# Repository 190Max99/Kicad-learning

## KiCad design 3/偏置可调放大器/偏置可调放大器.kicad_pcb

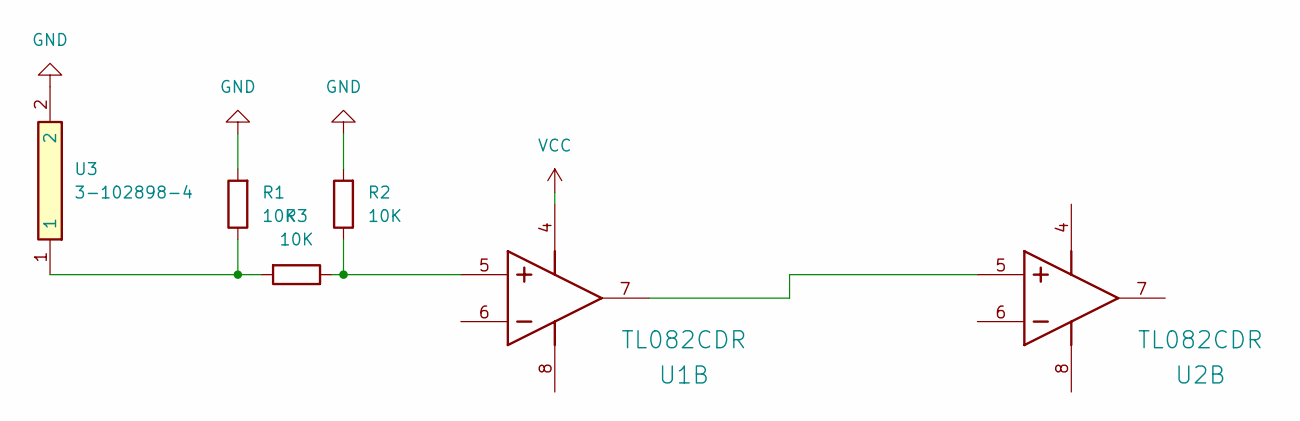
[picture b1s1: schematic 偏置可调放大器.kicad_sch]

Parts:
R1, R2, R3: 10K; R_01005_0402Metric
U1, U2: TL082CDR; voltage_gain 106.02 dB; MPN TL082CDR
U3: 3-102898-4; MPN 3-102898-4

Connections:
GND: R1.2, R2.2, U3.2
unnamed: R1.1, R3.2, U3.1
unnamed: R2.1, R3.1, U1.5 (IN2+)
unnamed 3: U1.7 (OUT2), U2.5 (IN2+); also elsewhere on the board
VCC: U1.4 (VCC-)

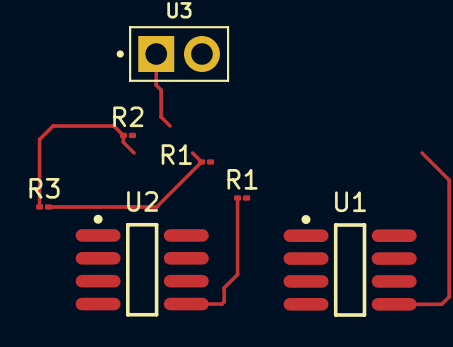
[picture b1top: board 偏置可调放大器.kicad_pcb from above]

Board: 2 copper layers, 7 parts (0 on the bottom side), 4 nets.

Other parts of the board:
R1#2: 100; R_01005_0402Metric

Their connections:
unnamed 3: R1#2.1; also elsewhere on the board

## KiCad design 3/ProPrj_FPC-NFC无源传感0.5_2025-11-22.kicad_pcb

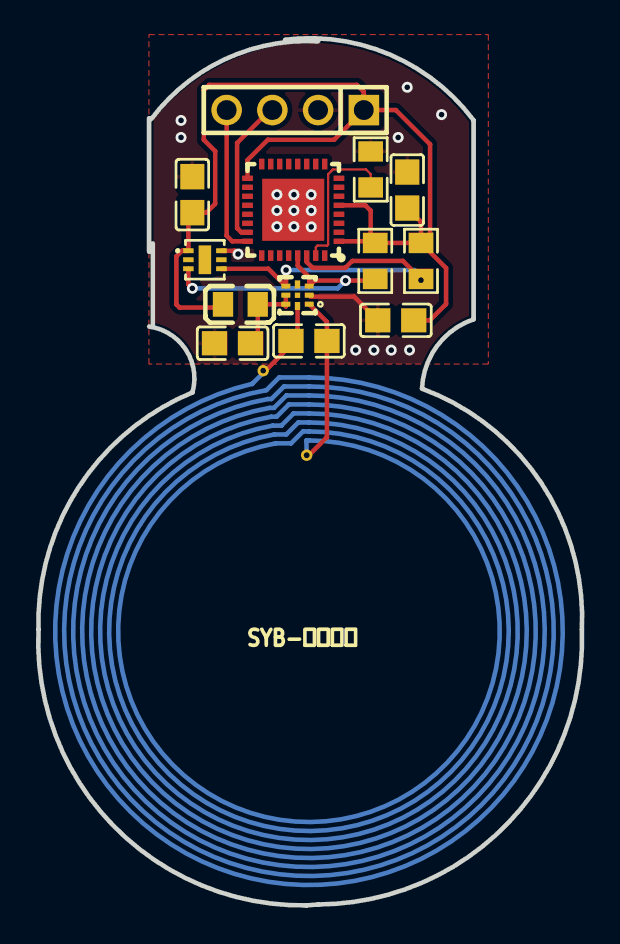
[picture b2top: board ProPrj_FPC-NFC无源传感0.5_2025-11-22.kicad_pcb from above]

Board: 2 copper layers, 30.2 x 48.2 mm, 14 parts (1 on the bottom side), 10 nets.

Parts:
A1: NFC天线
C1, C2, C4, C6, C7: C0805
H2: HDR-TH_4P-P2.54-V-M
L1: L0805
R1, R2, R3: R0805
U1: XQFN-8_L1.6-W1.6-P0.50-BL
U4: DFN-6_L2.0-W2.0-P0.50-TL-EP
U5: UFQFPN-32_L5.0-W5.0-P0.50-BL-EP

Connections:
3V3: C1.2, C4.2, C7.2, H2.1, L1.1, R1.2, R2.2, U4.1, U5.1, U5.5, U5.17
$1N694: C2.2, L1.2, U1.6, U1.7
$1N2079: A1.1, C6.2, U1.1
$1N2101: A1.2, C6.1, U1.8
$1N2525: R3.1, U5.31
GND: C1.1, C2.1, C4.1, C7.1, H2.2, R3.2, U1.2, U4.6, U5.33
SCL: R2.1, U1.3, U4.3, U5.29
SDA: R1.1, U1.5, U4.4, U5.30
SWCLK: H2.4, U5.24
SWDIO: H2.3, U5.23

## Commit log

2025-12-24 第一次提交,个人学习
2025-12-24 Add initial section for KICAD beginners practice
